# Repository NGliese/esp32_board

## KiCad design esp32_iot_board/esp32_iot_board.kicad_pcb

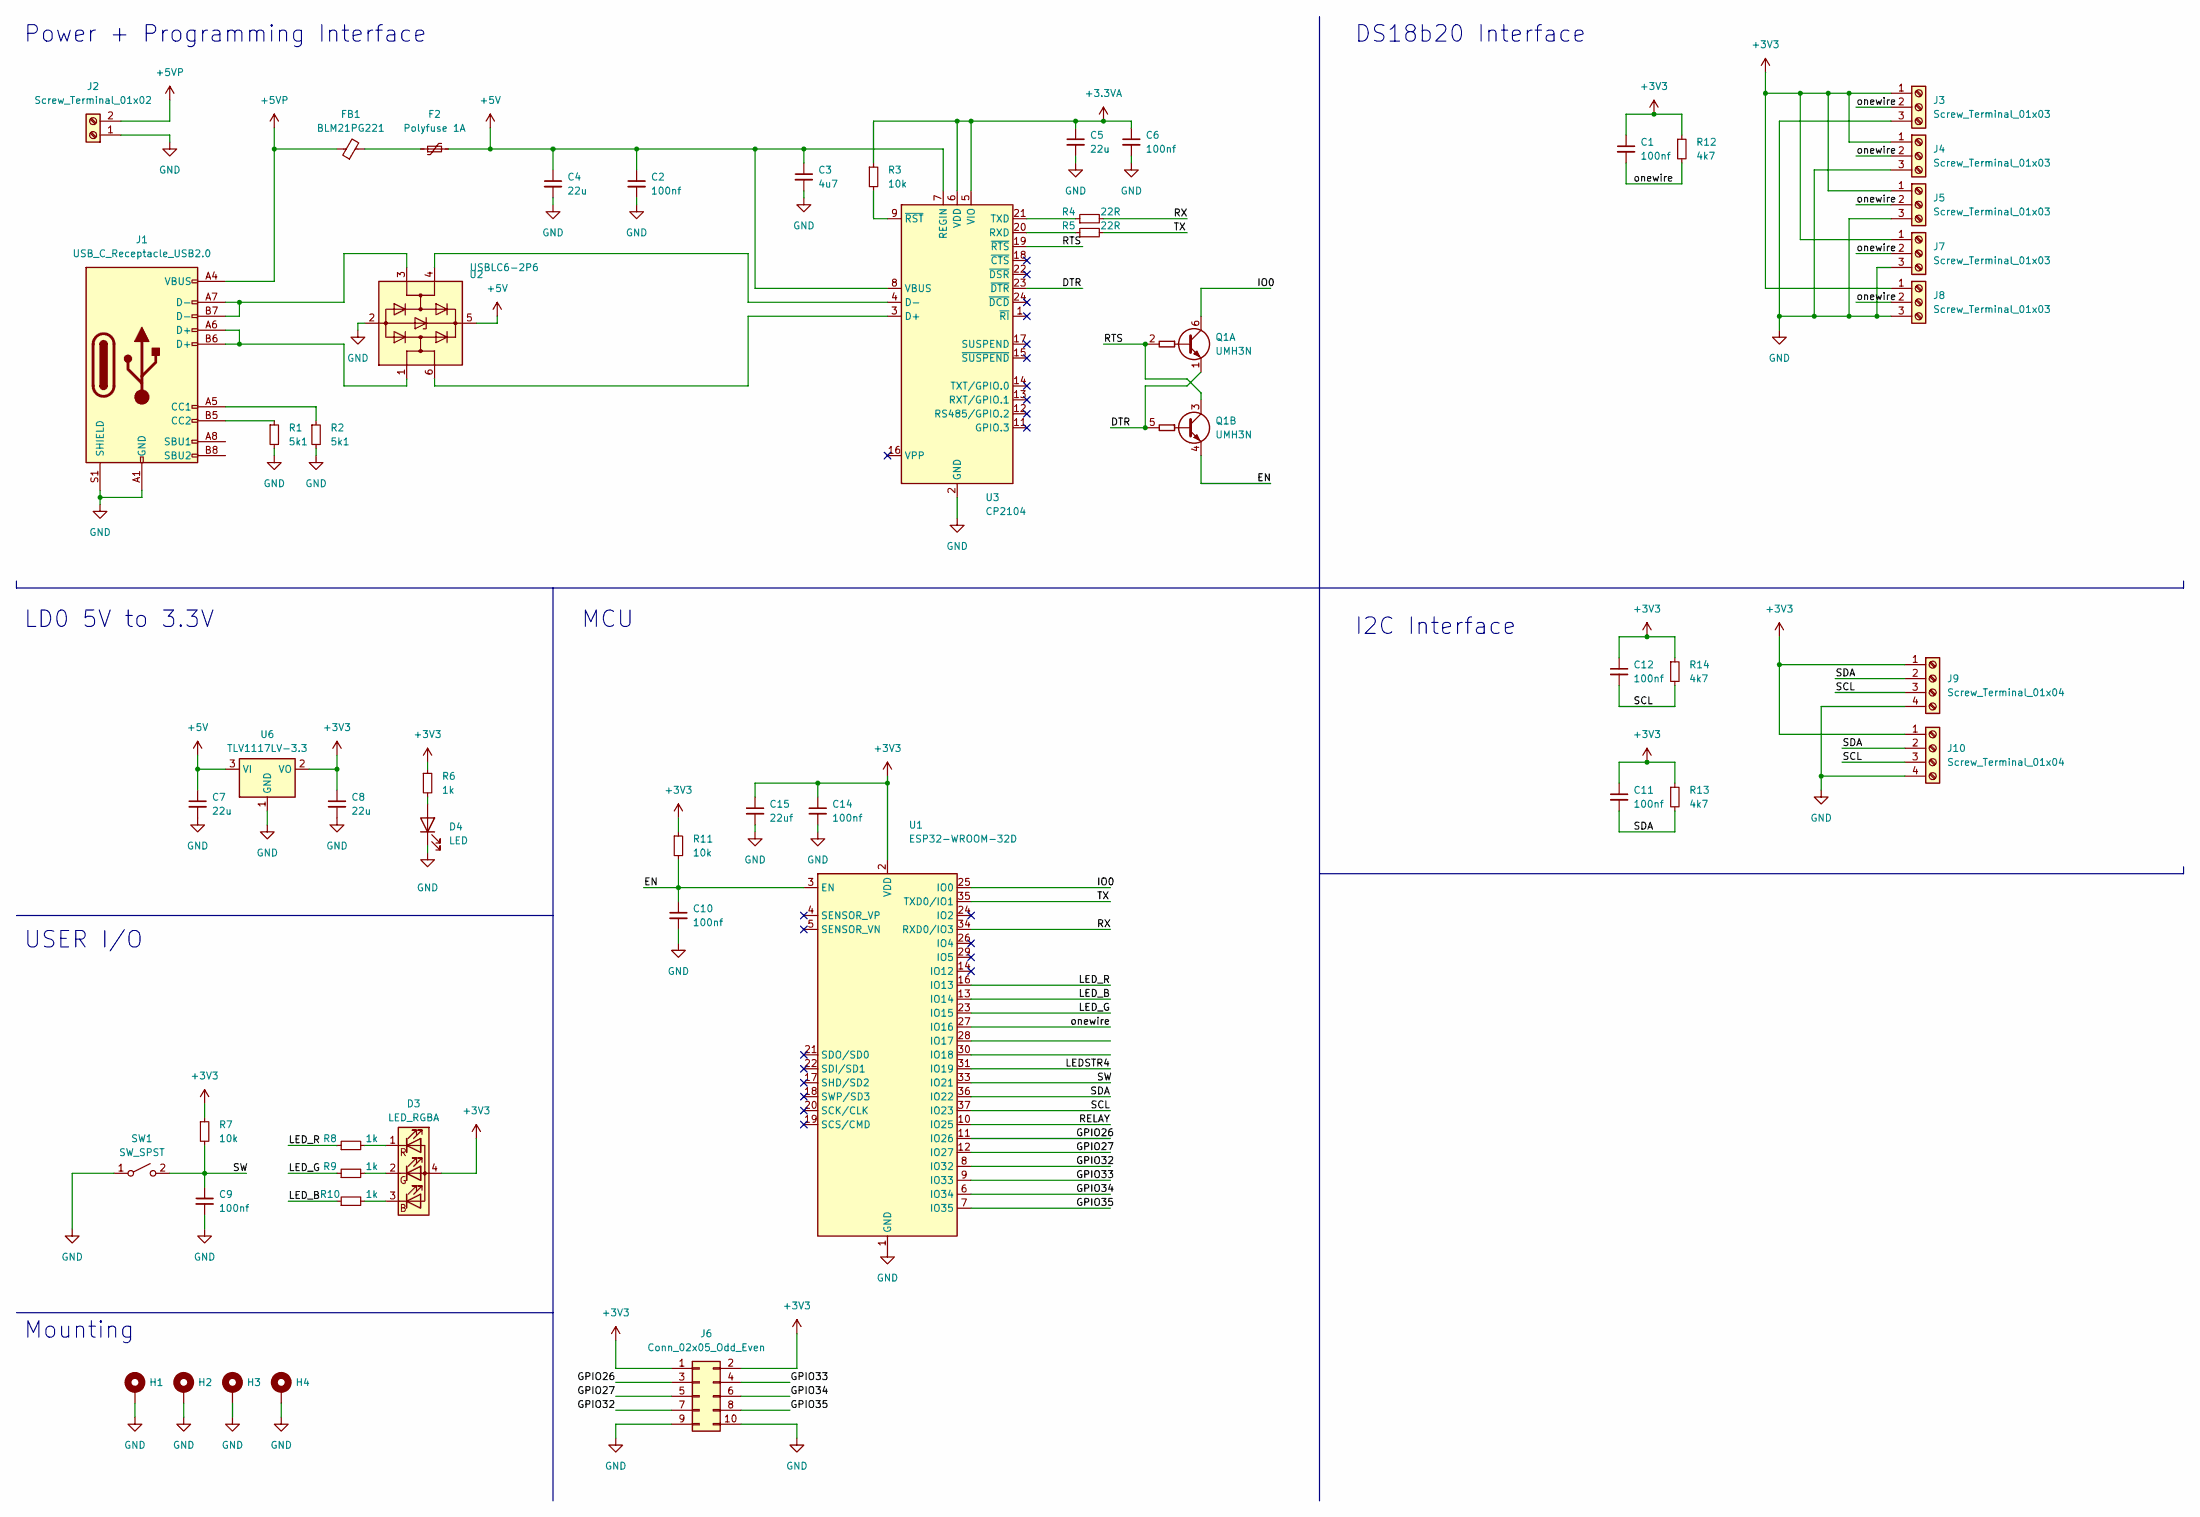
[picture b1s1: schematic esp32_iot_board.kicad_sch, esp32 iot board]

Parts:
C1, C2, C6, C9, C10, C11, C12, C14: 100nf; C_1206_3216Metric
C3: 4u7; C_1206_3216Metric
C4, C5, C7, C8: 22u; C_1206_3216Metric
C15: 22uf; C_1206_3216Metric
D3: LED_RGBA; LED_RGB_Wuerth-PLCC4_3.2x2.8mm_150141M173100
D4: LED; LED_1206_3216Metric
F2: Polyfuse 1A; Fuse_1206_3216Metric_Pad1.42x1.75mm_HandSolder
FB1: BLM21PG221; L_0603_1608Metric_Pad1.05x0.95mm_HandSolder
H1, H2, H3, H4: MountingHole_Pad; MountingHole_3.2mm_M3_Pad_Via
J1: USB_C_Receptacle_USB2.0; USB_C_Receptacle_HRO_TYPE-C-31-M-12
J2: Screw_Terminal_01x02; TerminalBlock_Phoenix_PT-1,5-2-5.0-H_1x02_P5.00mm_Horizontal
J3, J4, J5, J7, J8: Screw_Terminal_01x03; TerminalBlock_Phoenix_MKDS-3-3-5.08_1x03_P5.08mm_Horizontal
J6: Conn_02x05_Odd_Even; PinHeader_2x05_P2.54mm_Vertical
J9, J10: Screw_Terminal_01x04; TerminalBlock_Phoenix_MKDS-3-4-5.08_1x04_P5.08mm_Horizontal
Q1: UMH3N; SOT-363_SC-70-6
R1, R2: 5k1; R_1206_3216Metric
R3, R7, R11: 10k; R_1206_3216Metric
R4, R5: 22R; R_1206_3216Metric
R6, R8, R9, R10: 1k; R_1206_3216Metric
R12, R13, R14: 4k7; R_1206_3216Metric
SW1: SW_SPST; SW_Push_1P1T_NO_6x6mm_H9.5mm
U1: ESP32-WROOM-32D
U2: USBLC6-2P6; SOT-666
U3: CP2104; QFN-24-1EP_4x4mm_P0.5mm_EP2.6x2.6mm
U6: TLV1117LV-3.3; SOT-223-3_TabPin2

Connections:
+3.3VA: C5.1, C6.1, R3.1, U3.5 (VIO), U3.6 (VDD)
+3V3: C1.1, C8.1, C11.1, C12.1, C14.1, C15.1, D3.4 (A), J3.1, J4.1, J5.1, J6.1, J6.2, J7.1, J8.1, J9.1, J10.1, R6.1, R7.1, R11.1, R12.1, R13.1, R14.1, U1.2 (VDD), U6.2 (VO)
+5V: C2.1, C3.1, C4.1, C7.1, F2.2, U2.5 (VBUS), U3.7 (REGIN), U3.8 (VBUS), U6.3 (VI)
+5VP: FB1.1, J1.A4 (VBUS), J1.A9 (VBUS), J1.B4 (VBUS), J1.B9 (VBUS), J2.2
/DTR: Q1.1 (E1), Q1.5 (B2), U3.23 (~DTR)
/EN: C10.1, Q1.4 (E2), R11.2, U1.3 (EN)
/GPIO26: J6.3, U1.11 (IO26)
/GPIO27: J6.5, U1.12 (IO27)
/GPIO32: J6.7, U1.8 (IO32)
/GPIO33: J6.4, U1.9 (IO33)
/GPIO34: J6.6, U1.6 (IO34)
/GPIO35: J6.8, U1.7 (IO35)
/IO0: Q1.6 (C1), U1.25 (IO0)
/LEDSTR4: U1.31 (IO19)
/LED_B: R10.1, U1.13 (IO14)
/LED_G: R9.1, U1.23 (IO15)
/LED_R: R8.1, U1.16 (IO13)
/RELAY: U1.10 (IO25)
/RTS: Q1.2 (B1), Q1.3 (C2), U3.19 (~RTS)
/RX: R4.2, U1.34 (RXD0/IO3)
/SCL: C12.2, J9.3, J10.3, R14.2, U1.37 (IO23)
/SDA: C11.2, J9.2, J10.2, R13.2, U1.36 (IO22)
/SW: C9.1, R7.2, SW1.2 (B), U1.33 (IO21)
/TX: R5.2, U1.35 (TXD0/IO1)
/onewire: C1.2, J3.2, J4.2, J5.2, J7.2, J8.2, R12.2, U1.27 (IO16)
GND: C2.2, C3.2, C4.2, C5.2, C6.2, C7.2, C8.2, C9.2, C10.2, C14.2, C15.2, D4.1 (K), H1.1, H2.1, H3.1, H4.1, J1.A1 (GND), J1.A12 (GND), J1.B1 (GND), J1.B12 (GND), J1.S1 (SHIELD), J2.1, J3.3, J4.3, J5.3, J6.9, J6.10, J7.3, J8.3, J9.4, J10.4, R1.2, R2.2, SW1.1 (A), U1.1 (GND), U1.15 (GND), U1.38 (GND), U1.39 (GND), U2.2 (GND), U3.2 (GND), U3.25 (GND), U6.1 (GND)
unnamed: D3.3 (BK), R10.2
unnamed: D3.2 (GK), R9.2
unnamed: D3.1 (RK), R8.2
unnamed: D4.2 (A), R6.2
unnamed: F2.1, FB1.2
unnamed: J1.A5 (CC1), R2.1
unnamed: J1.B5 (CC2), R1.1
unnamed: J1.A6 (D+), J1.B6 (D+), U2.1 (I/O1)
unnamed: J1.A7 (D-), J1.B7 (D-), U2.3 (I/O2)
unnamed: U2.6 (I/O1), U3.3 (D+)
unnamed: U2.4 (I/O2), U3.4 (D-)
unnamed: R5.1, U3.20 (RXD)
unnamed: R4.1, U3.21 (TXD)
unnamed: R3.2, U3.9 (~RST)

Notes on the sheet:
I2C Interface
Mounting
LD0 5V to 3.3V
Power + Programming Interface
DS18b20 Interface
MCU
USER I/O

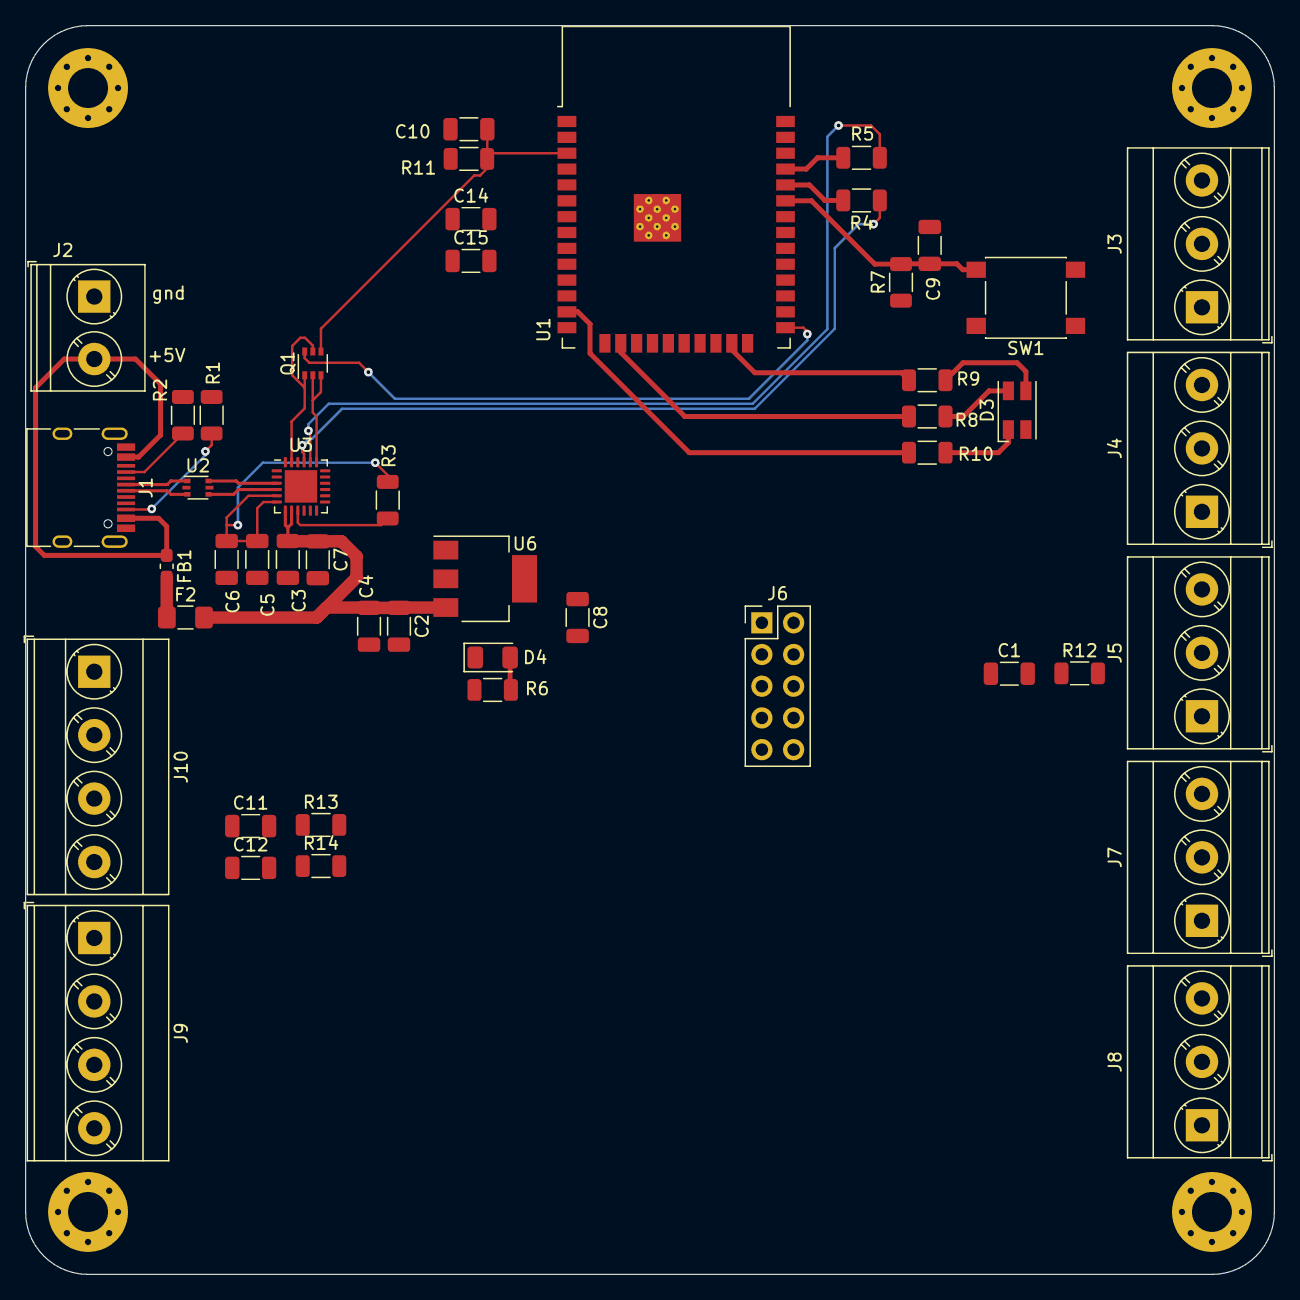
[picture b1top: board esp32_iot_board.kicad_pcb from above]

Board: 4 copper layers, 100.0 x 100.0 mm, 52 parts (0 on the bottom side), 38 nets.

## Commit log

2023-12-17 46_min into
2023-12-21 1.09hr
2023-12-23 1.30 min
2023-12-24 1.35 -> footprints assigned
2023-12-26 2.06h
2023-12-28 prog routed
2023-12-29 added i2c and onewire
